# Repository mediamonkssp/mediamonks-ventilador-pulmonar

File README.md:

# mediamonks-ventilator

Ventilator controller based on ATmega328 microcontroller

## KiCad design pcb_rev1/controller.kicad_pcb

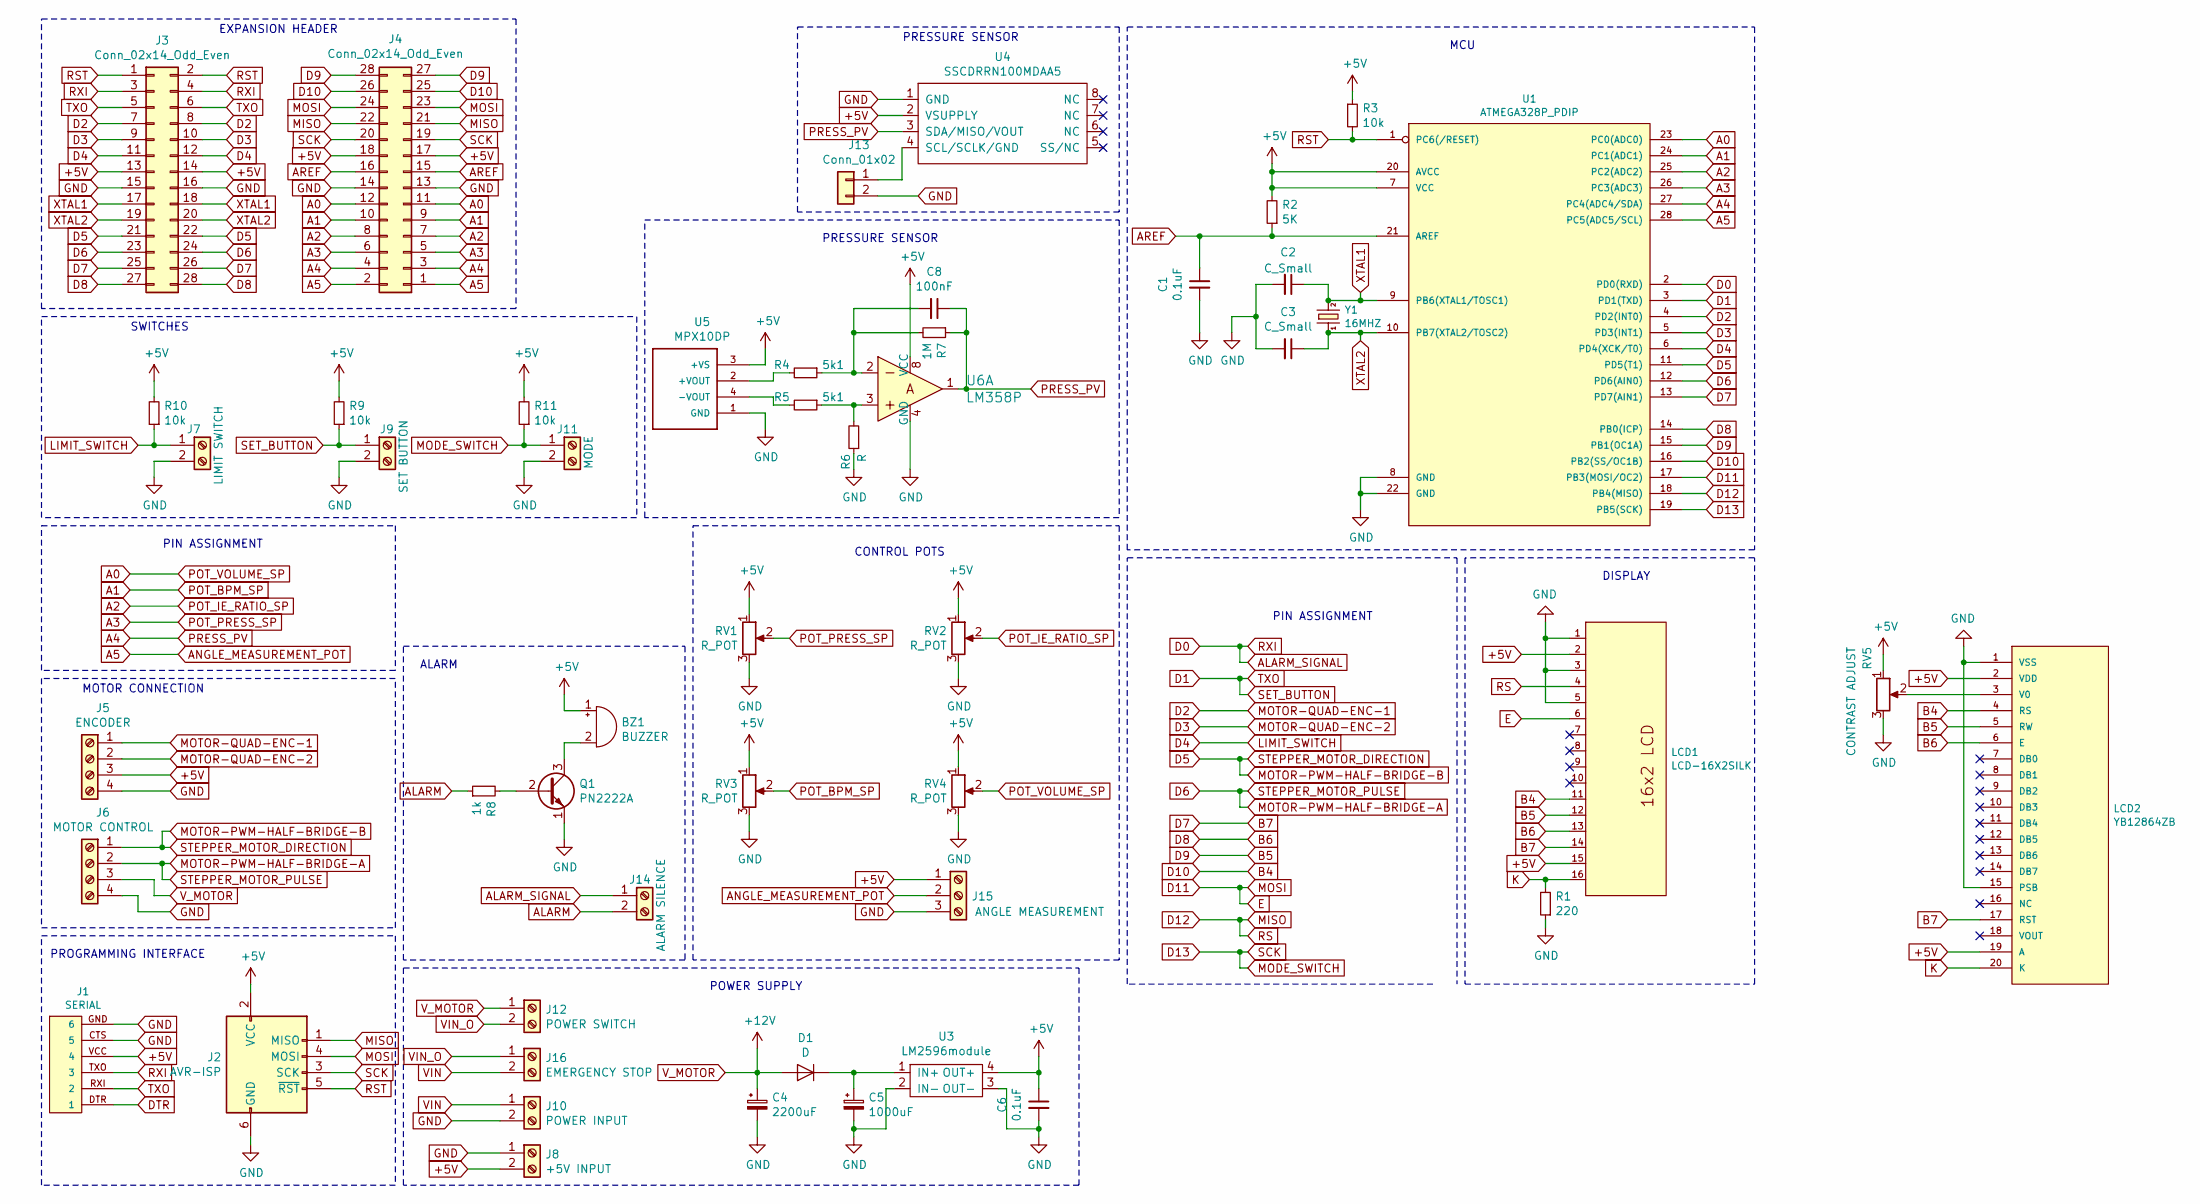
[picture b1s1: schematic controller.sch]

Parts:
BZ1: BUZZER; TerminalBlock_RND_205-00232_1x02_P5.08mm_Horizontal
C1, C6: 0.1uF; C_Disc_D3.8mm_W2.6mm_P2.50mm
C2, C3: C_Small; C_Disc_D3.8mm_W2.6mm_P2.50mm
C4: 2200uF; CP_Radial_D13.0mm_P7.50mm
C5: 1000uF; CP_Radial_D13.0mm_P7.50mm
C8: 100nF; C_Disc_D3.8mm_W2.6mm_P2.50mm
D1: D; D_DO-41_SOD81_P10.16mm_Horizontal
J1: SERIAL; FTDI_BASIC
J2: AVR-ISP; IDC-Header_2x03_P2.54mm_Vertical
J3, J4: Conn_02x14_Odd_Even; PinSocket_2x14_P2.54mm_Vertical
J5: ENCODER; TerminalBlock_RND_205-00234_1x04_P5.08mm_Horizontal
J6: MOTOR CONTROL; TerminalBlock_RND_205-00234_1x04_P5.08mm_Horizontal
J7: LIMIT SWITCH; TerminalBlock_RND_205-00232_1x02_P5.08mm_Horizontal
J8: +5V INPUT; TerminalBlock_RND_205-00232_1x02_P5.08mm_Horizontal
J9: SET BUTTON; TerminalBlock_RND_205-00232_1x02_P5.08mm_Horizontal
J10: POWER INPUT; TerminalBlock_RND_205-00232_1x02_P5.08mm_Horizontal
J11: MODE; TerminalBlock_RND_205-00232_1x02_P5.08mm_Horizontal
J12: POWER SWITCH; TerminalBlock_RND_205-00232_1x02_P5.08mm_Horizontal
J13: Conn_01x02; PinHeader_1x02_P2.54mm_Vertical
J14: ALARM SILENCE; TerminalBlock_RND_205-00232_1x02_P5.08mm_Horizontal
J15: ANGLE MEASUREMENT; TerminalBlock_RND_205-00233_1x03_P5.08mm_Horizontal
J16: EMERGENCY STOP; TerminalBlock_RND_205-00232_1x02_P5.08mm_Horizontal
LCD1: LCD-16X2SILK; LCD-16X2
LCD2: YB12864ZB
Q1: PN2222A; TO-92_Inline
R1: 220; R_Axial_DIN0204_L3.6mm_D1.6mm_P7.62mm_Horizontal
R2: 5K; R_Axial_DIN0204_L3.6mm_D1.6mm_P7.62mm_Horizontal
R3, R9, R10, R11: 10k; R_Axial_DIN0204_L3.6mm_D1.6mm_P7.62mm_Horizontal
R4, R5: 5k1; R_Axial_DIN0204_L3.6mm_D1.6mm_P7.62mm_Horizontal
R6: R; R_Axial_DIN0204_L3.6mm_D1.6mm_P7.62mm_Horizontal
R7: 1M; R_Axial_DIN0204_L3.6mm_D1.6mm_P7.62mm_Horizontal
R8: 1k; R_Axial_DIN0204_L3.6mm_D1.6mm_P7.62mm_Horizontal
RV1, RV2, RV3, RV4: R_POT; Potentiometer_Bourns_PTV09A-1_Single_Vertical
RV5: CONTRAST ADJUST; Potentiometer_Bourns_3296W_Vertical
U1: ATMEGA328P_PDIP; DIP28
U3: LM2596module; LM2596MODULE
U4: SSCDRRN100MDAA5; DIP-8_W13.3mm
U5: MPX10DP; SIP1067W46P254L2946H2934Q4P
U6: LM358P; DIP-8_W7.62mm_Socket_LongPads; MPN LM358P; Digi-Key_PN 296-1395-5-ND
Y1: 16MHZ; HC49US

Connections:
+5V: BZ1.1 (-), C6.1, J1.VCC (4), J2.2 (VCC), J3.13, J3.14, J4.17, J4.18, J5.3, J8.2, J15.1, LCD1.2 (VDD), LCD1.15 (A), LCD2.2 (VDD), LCD2.19 (A), R2.2, R3.1, R9.2, R10.2, R11.2, RV1.1, RV2.1, RV3.1, RV4.1, RV5.1, U1.7 (VCC), U1.20 (AVCC), U3.4 (OUT+), U4.2 (VSUPPLY), U5.3 (+VS), U6.8 (VCC)
A0: J4.11, J4.12, RV4.2, U1.23 (PC0(ADC0))
A1: J4.9, J4.10, RV3.2, U1.24 (PC1(ADC1))
A2: J4.7, J4.8, RV2.2, U1.25 (PC2(ADC2))
A3: J4.5, J4.6, RV1.2, U1.26 (PC3(ADC3))
A4: C8.1, J4.3, J4.4, R7.1, U1.27 (PC4(ADC4/SDA)), U4.3 (SDA/MISO/VOUT), U6.1
A5: J4.1, J4.2, J15.2, U1.28 (PC5(ADC5/SCL))
ALARM: J14.2, R8.1
ALARM_SIGNAL: J1.TXO (3), J3.3, J3.4, J14.1, U1.2 (PD0(RXD))
AREF: C1.1, J4.15, J4.16, R2.1, U1.21 (AREF)
B4: J4.25, J4.26, LCD1.11 (DB4), LCD2.4 (RS), U1.16 (PB2(SS/OC1B))
B5: J4.27, J4.28, LCD1.12 (DB5), LCD2.5 (RW), U1.15 (PB1(OC1A))
B6: J3.27, J3.28, LCD1.13 (DB6), LCD2.6 (E), U1.14 (PB0(ICP))
B7: J3.25, J3.26, LCD1.14 (DB7), LCD2.17 (RST), U1.13 (PD7(AIN1))
D1: J1.RXI (2), J3.5, J3.6, J9.1, R9.1, U1.3 (PD1(TXD))
D2: J3.7, J3.8, J5.1, U1.4 (PD2(INT0))
D3: J3.9, J3.10, J5.2, U1.5 (PD3(INT1))
D4: J3.11, J3.12, J7.1, R10.1, U1.6 (PD4(XCK/T0))
D5: J3.21, J3.22, J6.1, U1.11 (PD5(T1))
D6: J3.23, J3.24, J6.2, U1.12 (PD6(AIN0))
D11: J2.4 (MOSI), J4.23, J4.24, LCD1.6 (E), U1.17 (PB3(MOSI/OC2))
D12: J2.1 (MISO), J4.21, J4.22, LCD1.4 (RS), U1.18 (PB4(MISO))
D13: J2.3 (SCK), J4.19, J4.20, J11.1, R11.1, U1.19 (PB5(SCK))
DTR: J1.DTR (1)
GND: C1.2, C2.2, C3.2, C4.2, C5.2, C6.2, J1.CTS (5), J1.GND (6), J2.6 (GND), J3.15, J3.16, J4.13, J4.14, J5.4, J6.4, J7.2, J8.1, J9.2, J10.2, J11.2, J13.2, J15.3, LCD1.1 (VSS), LCD1.3 (VO), LCD1.5 (R/W), LCD2.1 (VSS), LCD2.15 (PSB), Q1.1 (E), R1.1, R6.1, RV1.3, RV2.3, RV3.3, RV4.3, RV5.3, U1.8 (GND), U1.22 (GND), U3.2 (IN-), U3.3 (OUT-), U4.1 (GND), U5.1 (GND), U6.4 (GND)
K: LCD1.16 (K), LCD2.20 (K), R1.2
unnamed: BZ1.2 (+), Q1.3 (C)
unnamed: C5.1, D1.1 (K), U3.1 (IN+)
unnamed: C8.2, R4.1, R7.2, U6.2
unnamed: J13.1, U4.4 (SCL/SCLK/GND)
unnamed: LCD2.3 (V0), RV5.2
unnamed: Q1.2 (B), R8.2
unnamed: R4.2, U5.2 (+VOUT)
unnamed: R5.1, R6.2, U6.3
unnamed: R5.2, U5.4 (-VOUT)
RST: J2.5 (~RST), J3.1, J3.2, R3.2, U1.1 (PC6(/RESET))
VIN: J10.1, J16.2
VIN_O: J12.2, J16.1
V_MOTOR: C4.1, D1.2 (A), J6.3, J12.1
XTAL1: C2.1, J3.17, J3.18, U1.9 (PB6(XTAL1/TOSC1)), Y1.2
XTAL2: C3.1, J3.19, J3.20, U1.10 (PB7(XTAL2/TOSC2)), Y1.1

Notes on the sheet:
DISPLAY
MCU
ALARM
PRESSURE SENSOR
PROGRAMMING INTERFACE
POWER SUPPLY
EXPANSION HEADER
MOTOR CONNECTION
SWITCHES
PIN ASSIGNMENT
CONTROL POTS

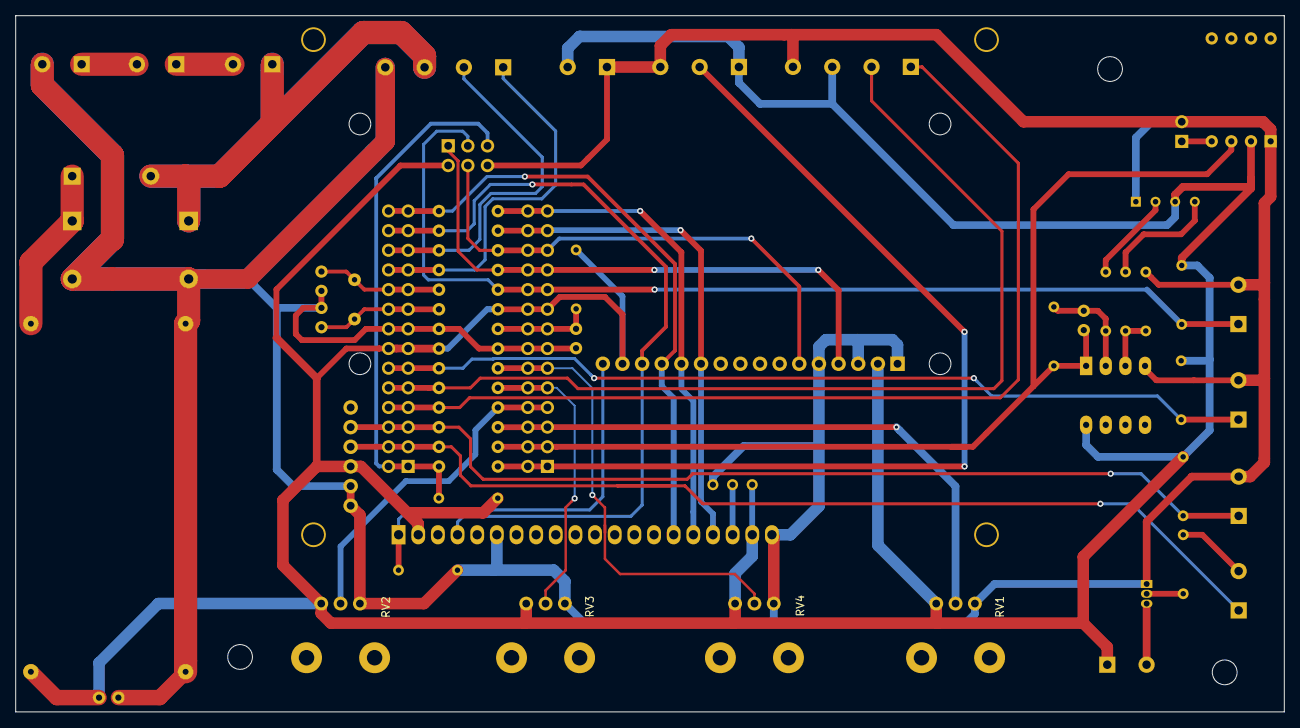
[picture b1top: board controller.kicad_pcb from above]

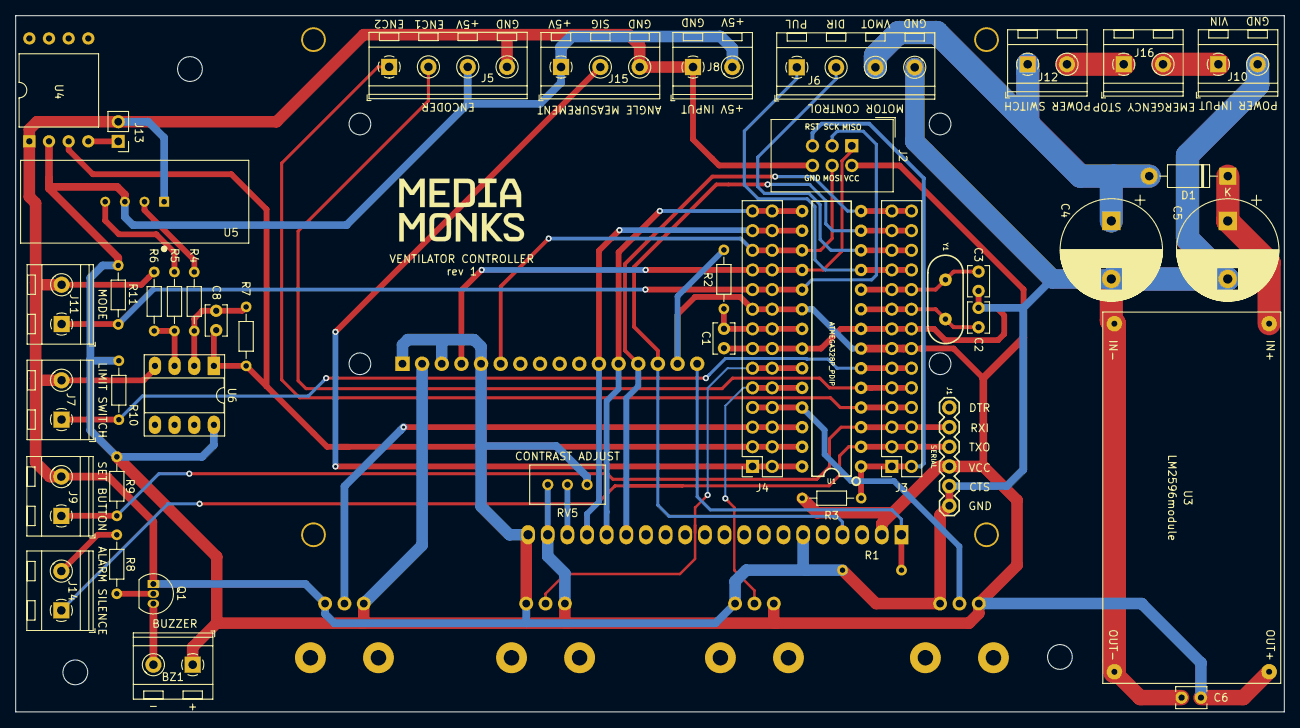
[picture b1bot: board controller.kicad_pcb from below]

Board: 2 copper layers, 164.0 x 90.0 mm, 50 parts (44 on the bottom side), 40 nets.

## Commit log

2020-04-09 Create LICENSE
2020-04-09 pcb files added
2020-04-09 images uploaded
2020-04-09 schematic.pdf added
2020-04-09 readme update
